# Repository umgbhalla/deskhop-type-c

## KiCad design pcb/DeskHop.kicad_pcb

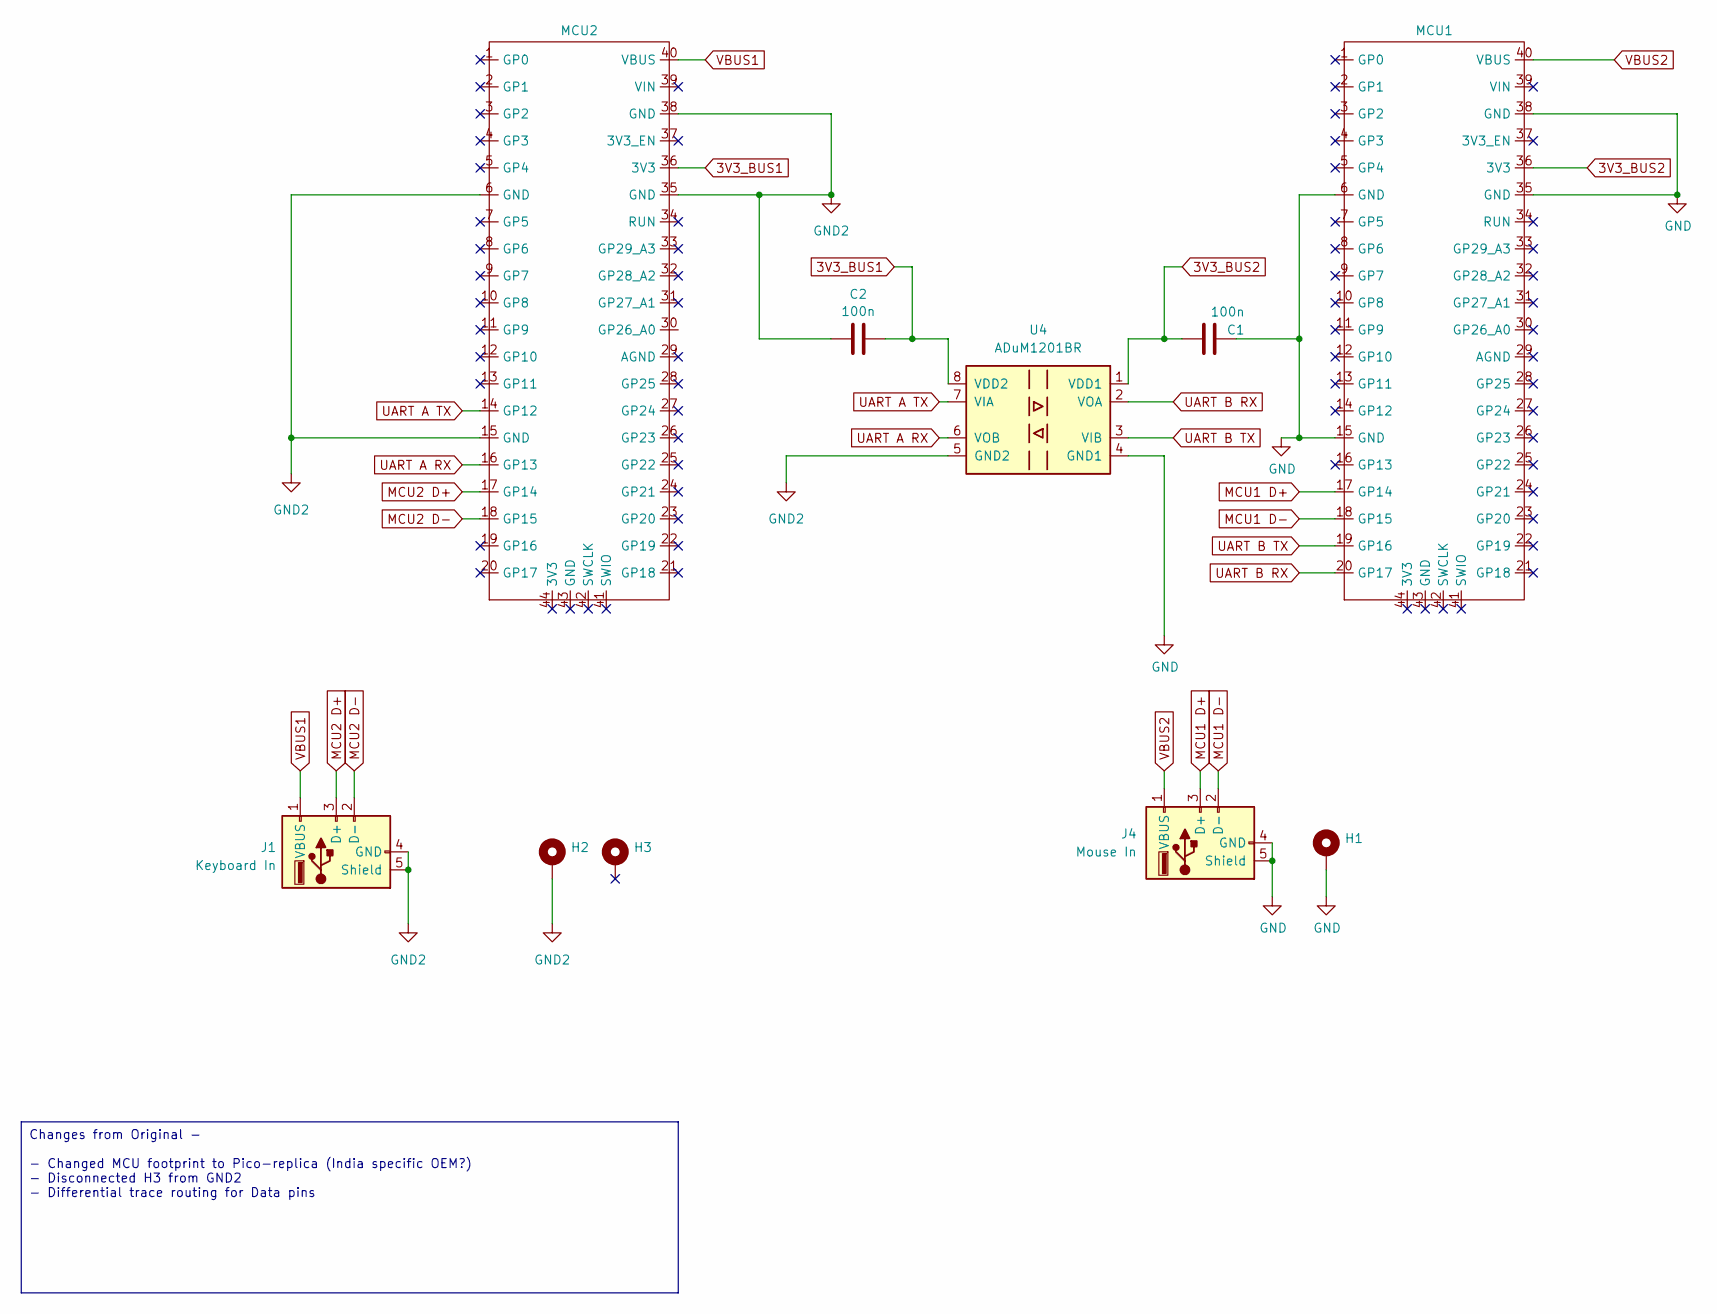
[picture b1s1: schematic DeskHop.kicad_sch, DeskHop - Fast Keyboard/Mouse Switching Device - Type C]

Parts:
C1, C2: 100n; C_1206_3216Metric_Pad1.33x1.80mm_HandSolder
H1, H2: MountingHole_Pad; MountingHole_2.7mm_M2.5_Pad_TopBottom
H3: MountingHole_Pad; MountingHole_2.7mm_M2.5_Pad_TopOnly
J1: Keyboard In; USB_A_Molex_67643_Horizontal
J4: Mouse In; USB_A_Molex_67643_Horizontal
MCU1, MCU2: Pico_like
U4: ADuM1201BR; SOIC-8_3.9x4.9mm_P1.27mm

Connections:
3V3_BUS1: C2.2, MCU2.36 (3V3), U4.8 (VDD2)
3V3_BUS2: C1.1, MCU1.36 (3V3), U4.1 (VDD1)
GND: C1.2, H1.1, J4.4 (GND), J4.5 (Shield), MCU1.6 (GND), MCU1.15 (GND), MCU1.35 (GND), MCU1.38 (GND), U4.4 (GND1)
GND2: C2.1, H2.1, J1.4 (GND), J1.5 (Shield), MCU2.6 (GND), MCU2.15 (GND), MCU2.35 (GND), MCU2.38 (GND), U4.5 (GND2)
MCU1 D+: J4.3 (D+), MCU1.17 (GP14)
MCU1 D-: J4.2 (D-), MCU1.18 (GP15)
MCU2 D+: J1.3 (D+), MCU2.17 (GP14)
MCU2 D-: J1.2 (D-), MCU2.18 (GP15)
UART A RX: MCU2.16 (GP13), U4.6 (VOB)
UART A TX: MCU2.14 (GP12), U4.7 (VIA)
UART B RX: MCU1.20 (GP17), U4.2 (VOA)
UART B TX: MCU1.19 (GP16), U4.3 (VIB)
VBUS1: J1.1 (VBUS), MCU2.40 (VBUS)
VBUS2: J4.1 (VBUS), MCU1.40 (VBUS)

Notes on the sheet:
Changes from Original - - Changed MCU footprint to Pico-replica (India specific OEM?) - Disconnected H3 from GND2 - Differential trace routing for Data pins

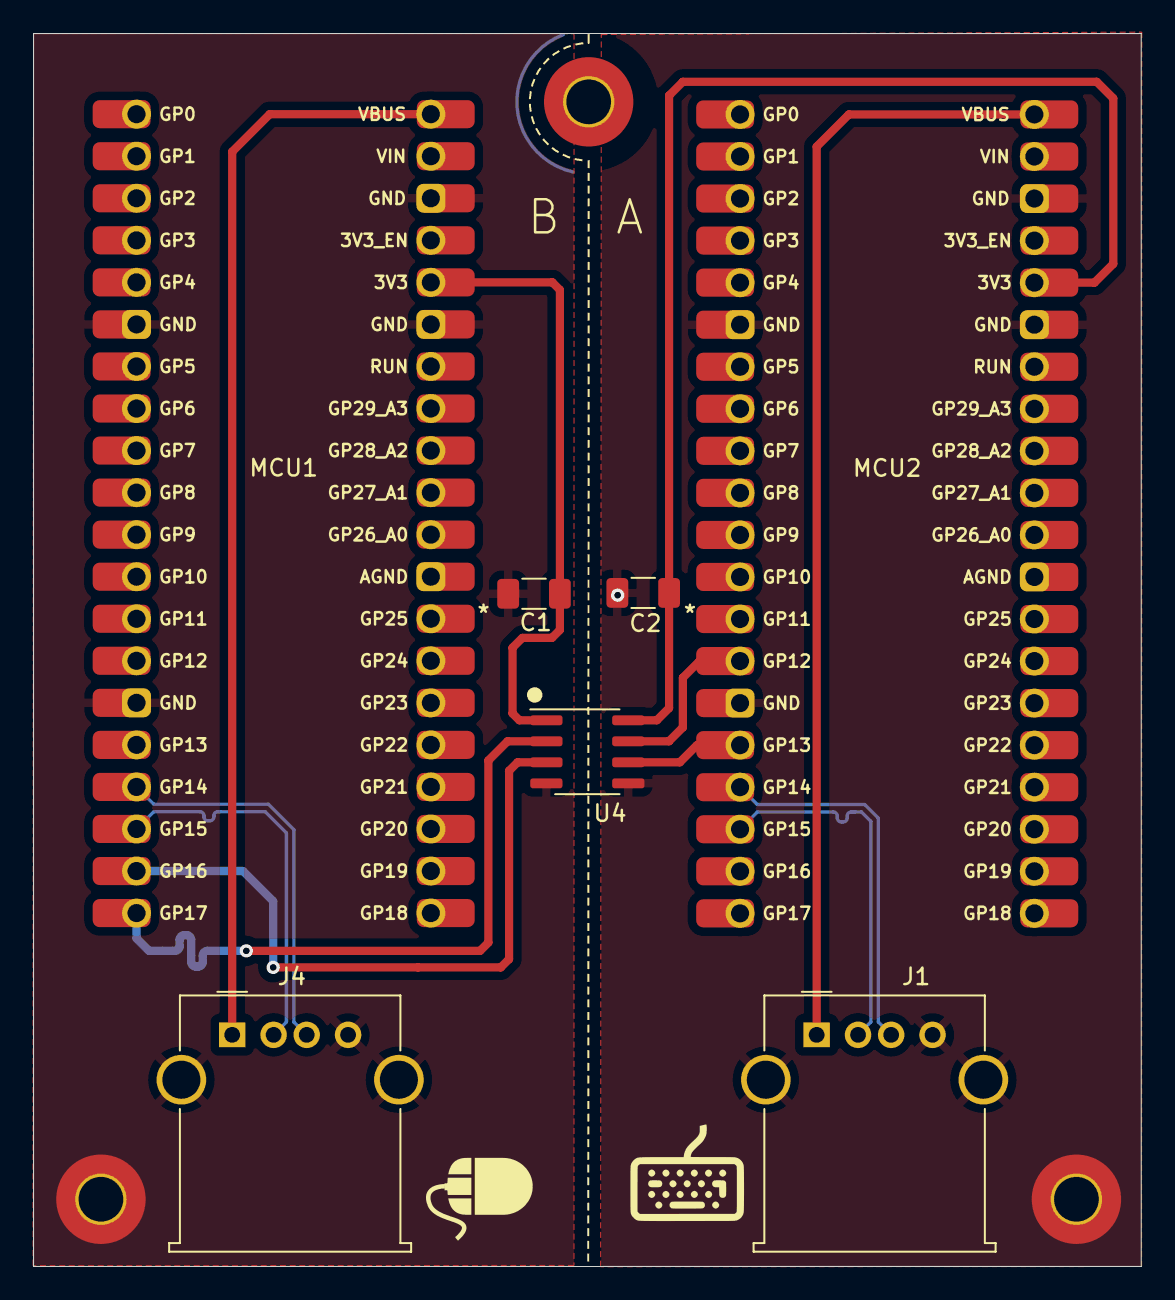
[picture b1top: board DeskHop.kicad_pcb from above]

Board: 2 copper layers, 66.9 x 74.5 mm, 10 parts (0 on the bottom side), 14 nets.

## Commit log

2024-02-20 Changed design to Type C pico copy
    Modifications done to adapt design to Type C version of Pico-copy available in India. Detail changes in PCB Schematics.
2024-05-03 reverted back to orignal GPIO for MCU 1
2024-05-03 GND fill error sorted
